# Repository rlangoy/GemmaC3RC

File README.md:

# GemmaC3RC
 Gemma RC controller using ESP32-C3 Super mini module

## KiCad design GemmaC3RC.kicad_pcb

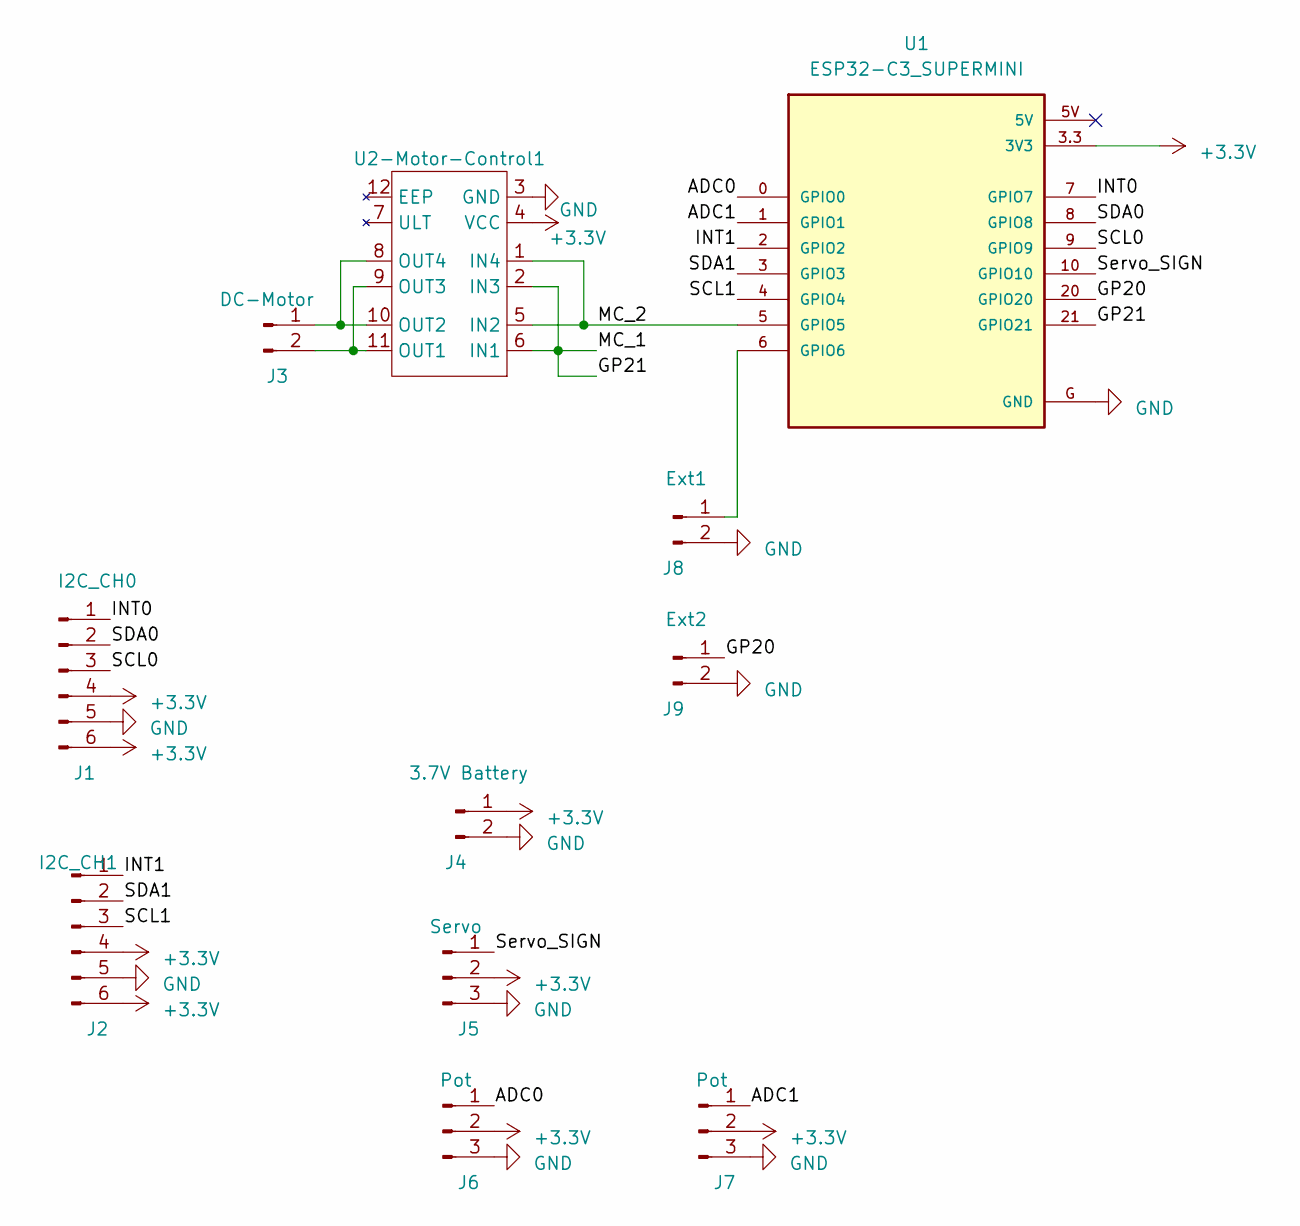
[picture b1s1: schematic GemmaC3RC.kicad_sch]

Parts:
J1: I2C_CH0; SIP-6
J2: I2C_CH1; SIP-6
J3: DC-Motor; PinHeader_1x02_P2.54mm_Vertical
J4: 3.7V Battery; PinHeader_1x02_P2.54mm_Vertical
J5: Servo; PinHeader_1x03_P2.54mm_Vertical
J6, J7: Pot; PinSocket_1x03_P2.54mm_Vertical
J8: Ext1; PinHeader_1x02_P2.54mm_Vertical
J9: Ext2; PinHeader_1x02_P2.54mm_Vertical
U1: ESP32-C3_SUPERMINI; MODULE_ESP32-C3_SUPERMINI
U2-Motor-Control1: DIP-12_600_ELL

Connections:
+3.3V: J1.4, J1.6, J2.4, J2.6, J4.1, J5.2, J6.2, J7.2, U1.3.3 (3V3), U2-Motor-Control1.4 (VCC)
/ADC0: J6.1, U1.0 (GPIO0)
/ADC1: J7.1, U1.1 (GPIO1)
/GP20: J9.1, U1.20 (GPIO20)
/GP21: U1.21 (GPIO21), U2-Motor-Control1.2 (IN3), U2-Motor-Control1.6 (IN1)
/INT0: J1.1, U1.7 (GPIO7)
/INT1: J2.1, U1.2 (GPIO2)
/MC_2: U1.5 (GPIO5), U2-Motor-Control1.1 (IN4), U2-Motor-Control1.5 (IN2)
/SCL0: J1.3, U1.9 (GPIO9)
/SCL1: J2.3, U1.4 (GPIO4)
/SDA0: J1.2, U1.8 (GPIO8)
/SDA1: J2.2, U1.3 (GPIO3)
/Servo_SIGN: J5.1, U1.10 (GPIO10)
GND: J1.5, J2.5, J4.2, J5.3, J6.3, J7.3, J8.2, J9.2, U1.G (GND), U2-Motor-Control1.3 (GND)
unnamed: J3.1, U2-Motor-Control1.8 (OUT4), U2-Motor-Control1.10 (OUT2)
unnamed: J3.2, U2-Motor-Control1.9 (OUT3), U2-Motor-Control1.11 (OUT1)
unnamed: J8.1, U1.6 (GPIO6)

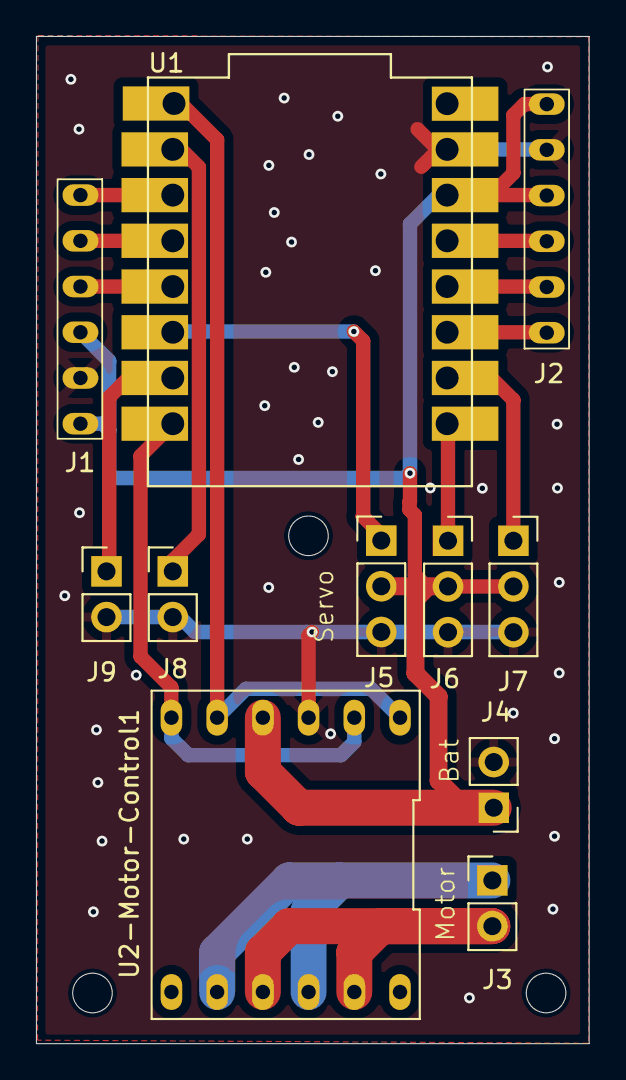
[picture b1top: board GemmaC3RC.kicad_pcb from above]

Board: 2 copper layers, 30.7 x 56.0 mm, 11 parts (0 on the bottom side), 17 nets.

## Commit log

2024-05-30 Initital commit
    Initial commit version 1.0
2024-11-26 Updated to ver 1.1
    Bat is conneced to 3.3V and In1 io pin changed
